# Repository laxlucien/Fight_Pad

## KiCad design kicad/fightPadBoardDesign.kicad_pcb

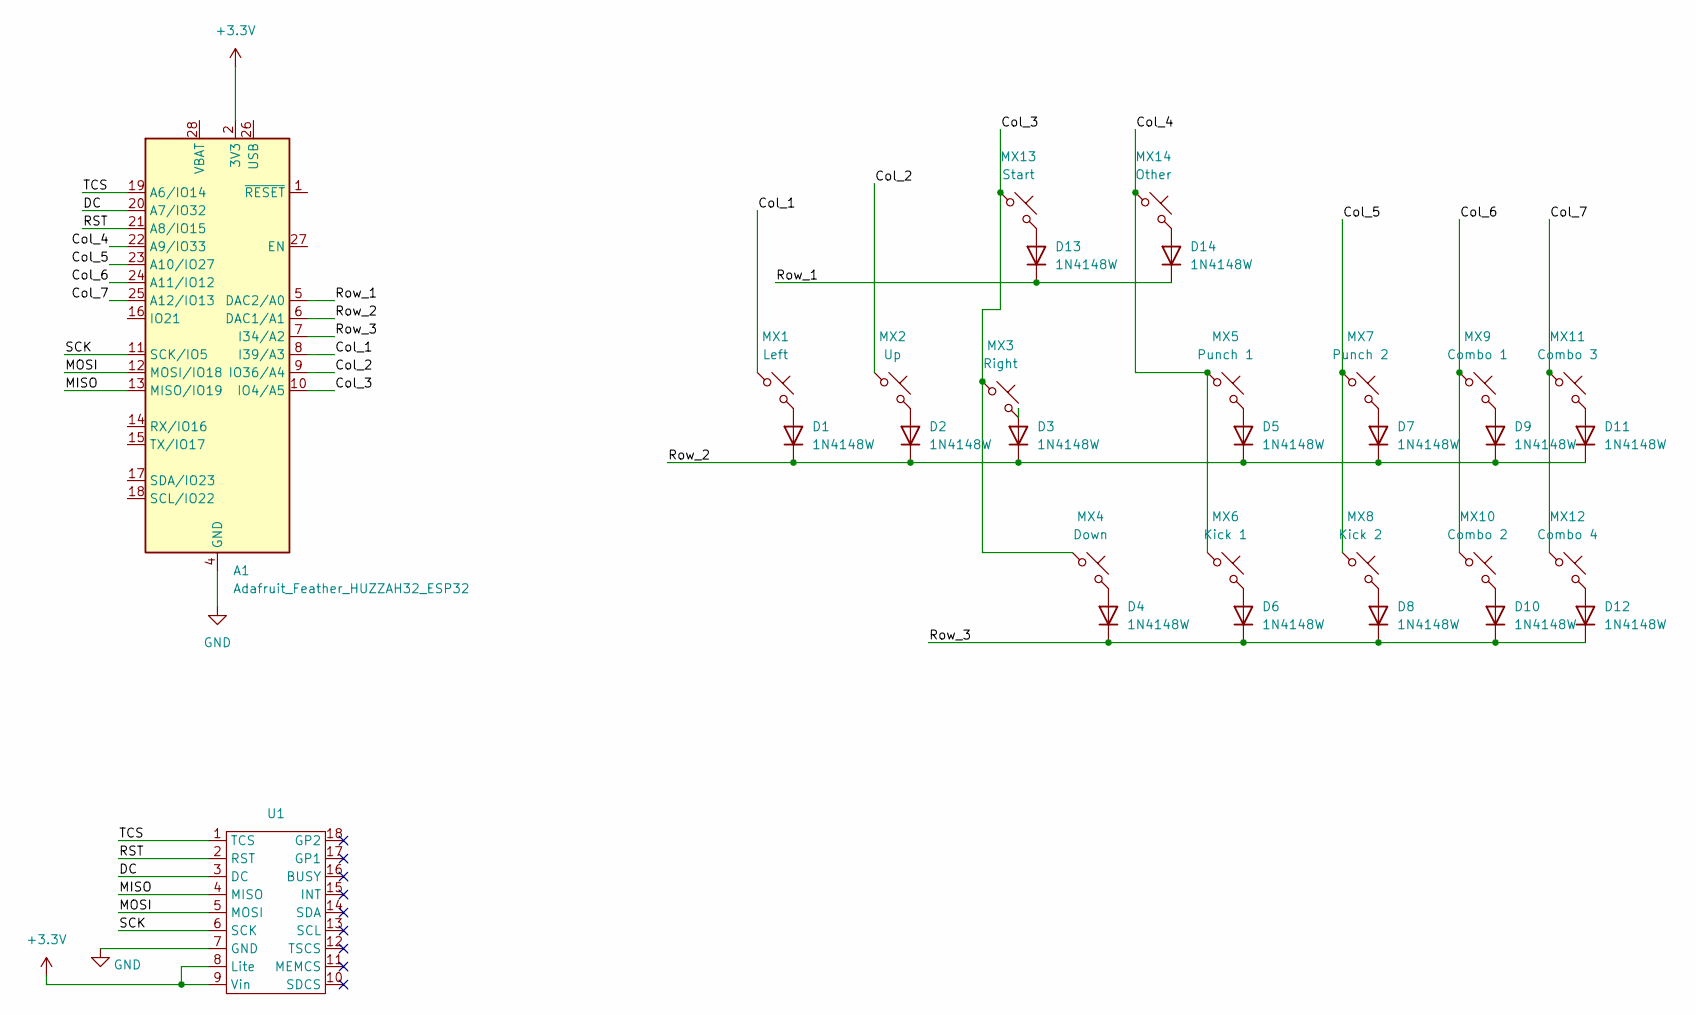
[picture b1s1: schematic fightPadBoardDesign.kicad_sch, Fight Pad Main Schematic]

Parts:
A1: Adafruit_Feather_HUZZAH32_ESP32; Adafruit_Feather
D1, D2, D3, D4, D5, D6, D7, D8, D9, D10, D11, D12, D13, D14: 1N4148W; D_SOD-123
MX1: Left; SW_MX_1u
MX2: Up; SW_MX_1u
MX3: Right; SW_MX_1u
MX4: Down; SW_MX_1u
MX5: Punch 1; SW_MX_1u
MX6: Kick 1; SW_MX_1u
MX7: Punch 2; SW_MX_1u
MX8: Kick 2; SW_MX_1u
MX9: Combo 1; SW_MX_1u
MX10: Combo 2; SW_MX_1u
MX11: Combo 3; SW_MX_1u
MX12: Combo 4; SW_MX_1u
MX13: Start; SW_MX_1u
MX14: Other; SW_MX_1u
U1: EYESPI

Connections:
+3.3V: A1.2 (3V3), U1.8 (Lite), U1.9 (Vin)
/Col_1: A1.8 (I39/A3), MX1.1
/Col_2: A1.9 (IO36/A4), MX2.1
/Col_3: A1.10 (IO4/A5), MX3.1, MX4.1, MX13.1
/Col_4: A1.22 (A9/IO33), MX5.1, MX6.1, MX14.1
/Col_5: A1.23 (A10/IO27), MX7.1, MX8.1
/Col_6: A1.24 (A11/IO12), MX9.1, MX10.1
/Col_7: A1.25 (A12/IO13), MX11.1, MX12.1
/DC: A1.20 (A7/IO32), U1.3 (DC)
/MISO: A1.13 (MISO/IO19), U1.4 (MISO)
/MOSI: A1.12 (MOSI/IO18), U1.5 (MOSI)
/RST: A1.21 (A8/IO15), U1.2 (RST)
/Row_1: A1.5 (DAC2/A0), D13.1 (K), D14.1 (K)
/Row_2: A1.6 (DAC1/A1), D1.1 (K), D2.1 (K), D3.1 (K), D5.1 (K), D7.1 (K), D9.1 (K), D11.1 (K)
/Row_3: A1.7 (I34/A2), D4.1 (K), D6.1 (K), D8.1 (K), D10.1 (K), D12.1 (K)
/SCK: A1.11 (SCK/IO5), U1.6 (SCK)
/TCS: A1.19 (A6/IO14), U1.1 (TCS)
GND: A1.4 (GND), U1.7 (GND)
unnamed: D1.2 (A), MX1.2
unnamed: D2.2 (A), MX2.2
unnamed: D3.2 (A), MX3.2
unnamed: D4.2 (A), MX4.2
unnamed: D5.2 (A), MX5.2
unnamed: D6.2 (A), MX6.2
unnamed: D7.2 (A), MX7.2
unnamed: D8.2 (A), MX8.2
unnamed: D9.2 (A), MX9.2
unnamed: D10.2 (A), MX10.2
unnamed: D11.2 (A), MX11.2
unnamed: D12.2 (A), MX12.2
unnamed: D13.2 (A), MX13.2
unnamed: D14.2 (A), MX14.2

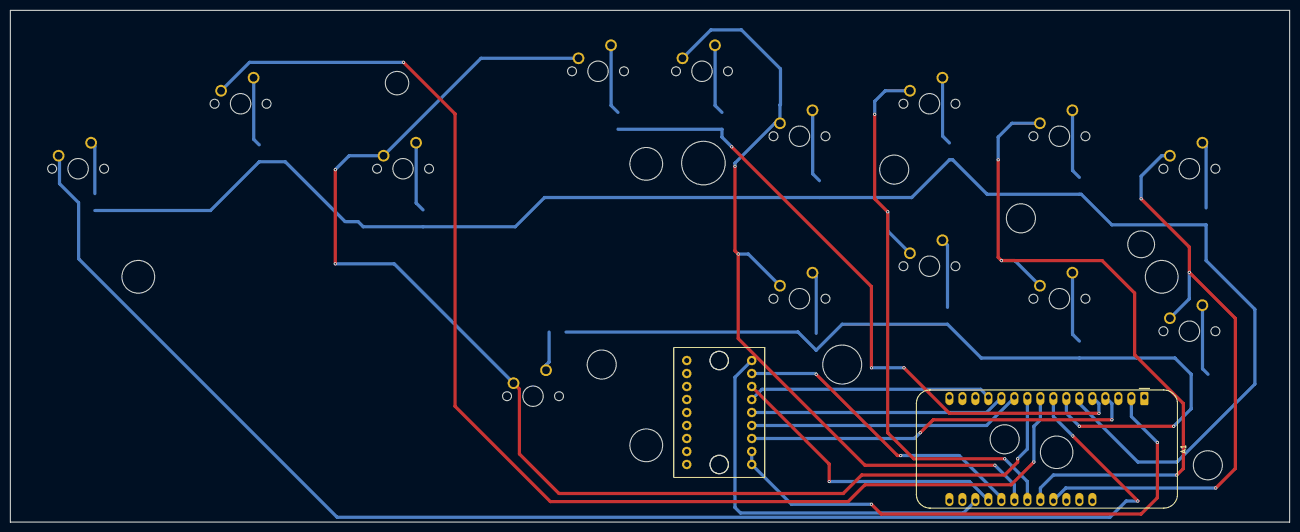
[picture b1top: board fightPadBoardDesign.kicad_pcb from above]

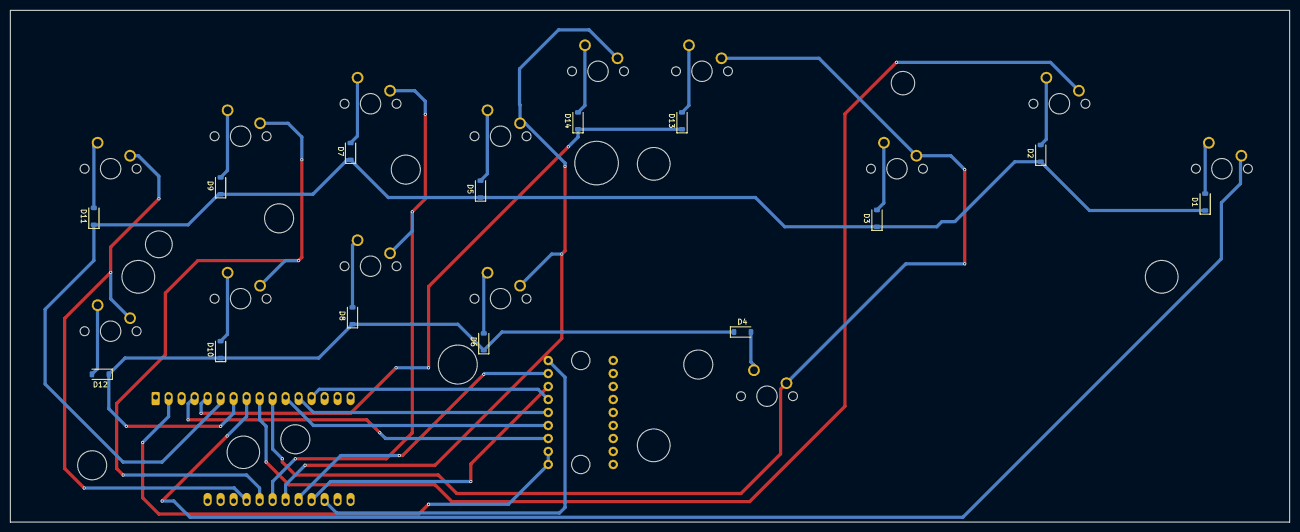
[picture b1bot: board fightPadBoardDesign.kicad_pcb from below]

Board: 2 copper layers, 250.0 x 100.0 mm, 30 parts (14 on the bottom side), 32 nets.

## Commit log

2026-05-09 gitignore added
2026-05-09 Main Shematic done and uploaded with footprints assigned
2026-05-10 Added layout and got the placement correct with housing
2026-05-10 Added current housing drawings
2026-05-14 Updated housing drawings to include inserts and screws
2026-05-17 Updated bottom housing plate
2026-05-17 Updated routing and added board mount holes
2026-05-17 made bambu file for all assembly pieces
2026-05-17 added 3mf files for stls for housing
